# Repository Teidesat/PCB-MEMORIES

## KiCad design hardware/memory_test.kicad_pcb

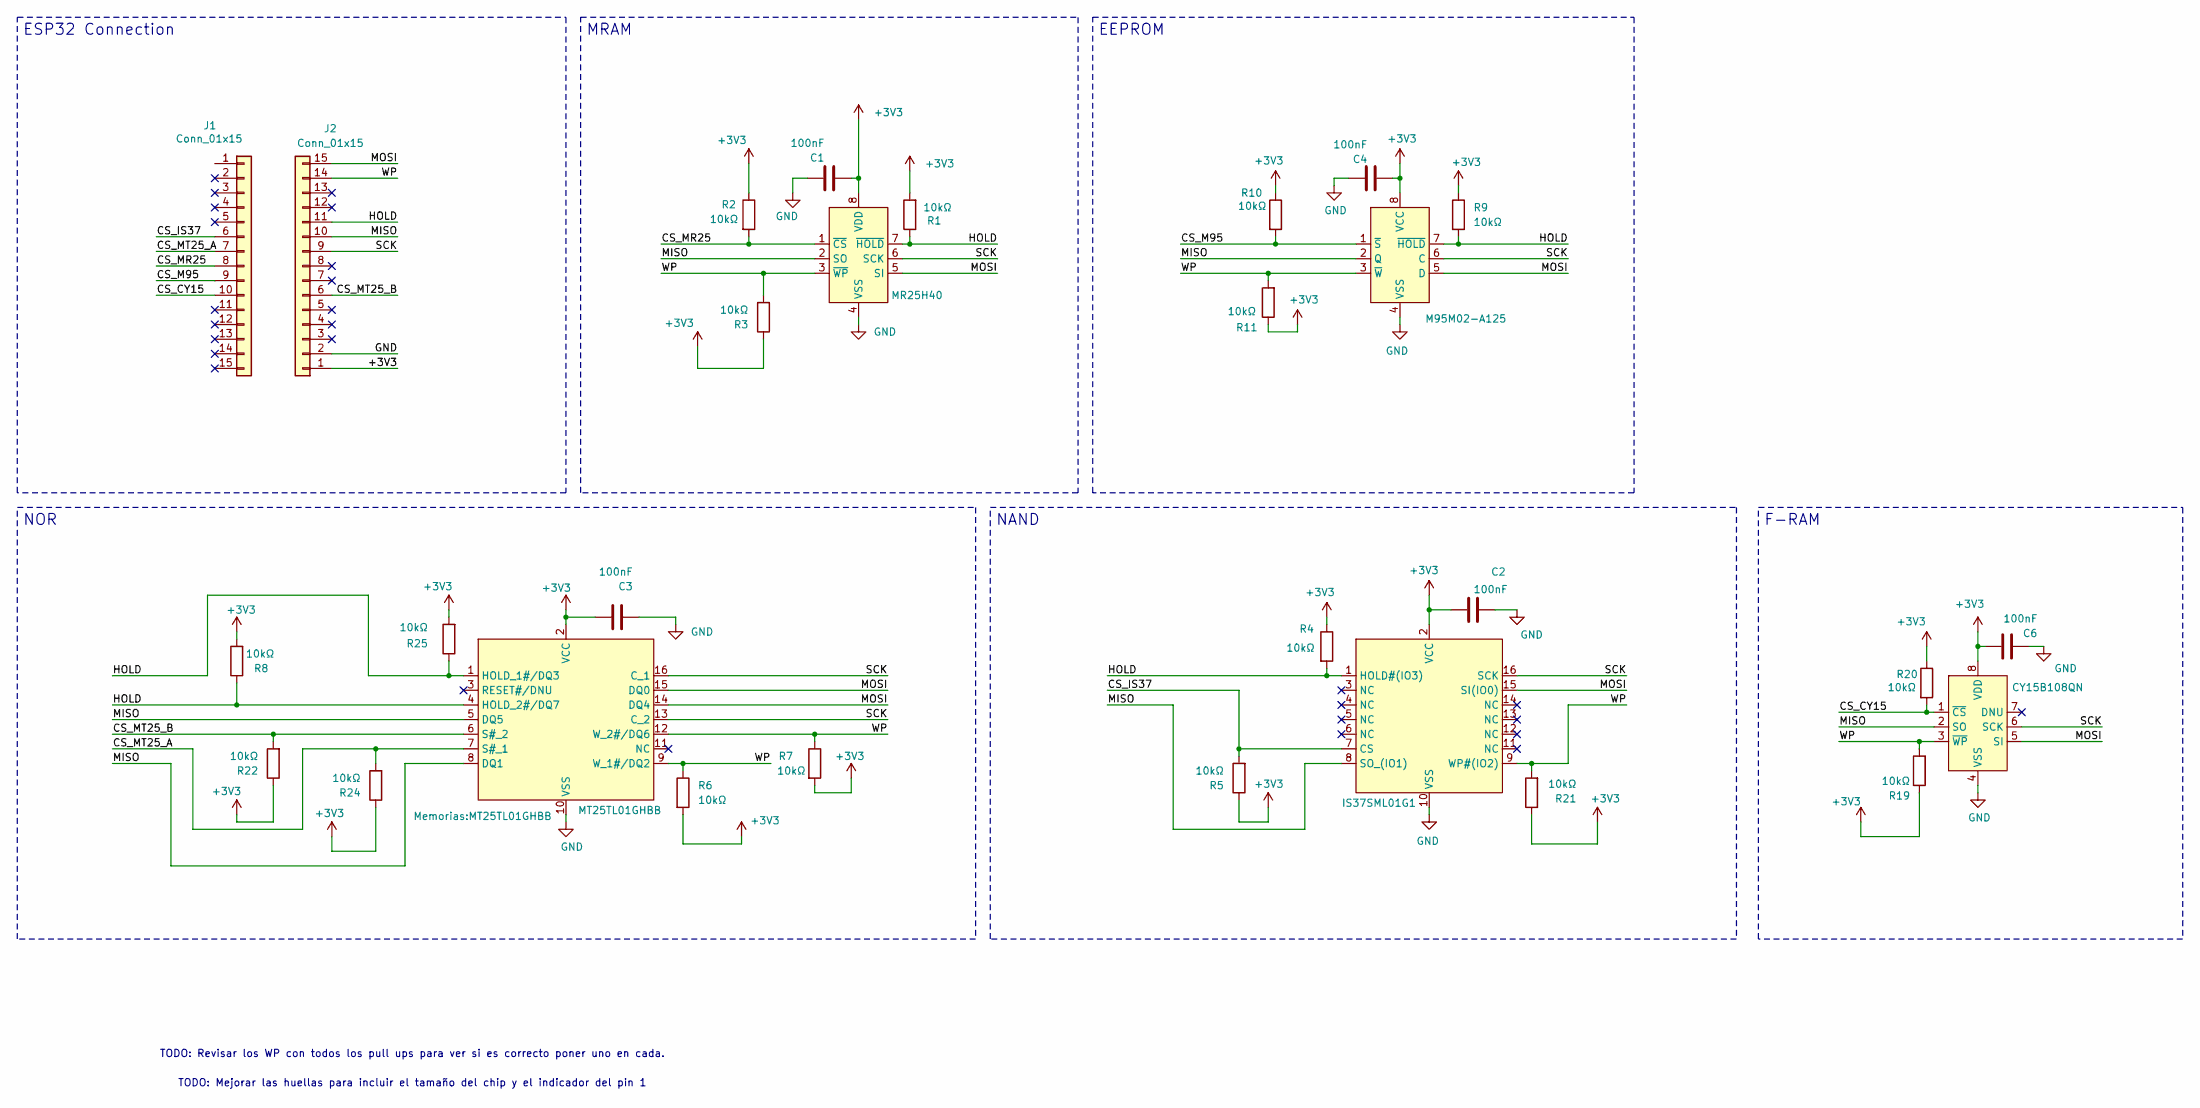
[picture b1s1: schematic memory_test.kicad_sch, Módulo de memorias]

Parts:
C1, C2, C3, C4, C6: 100nF; C_0805_2012Metric_Pad1.18x1.45mm_HandSolder
J1, J2: Conn_01x15; PinSocket_1x15_P2.54mm_Vertical
R1, R2, R3, R4, R5, R6, R7, R8, R9, R10, R11, R19, R20, R21, R22, R24, R25: 10kΩ; R_0805_2012Metric_Pad1.20x1.40mm_HandSolder
U1: MR25H40
U2: IS37SML01G1
U3: MT25TL01GHBB
U4: M95M02-A125
U6: CY15B108QN

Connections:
+3V3: C1.2, C2.2, C3.2, C4.2, C6.1, J2.1, R1.2, R2.1, R3.1, R4.1, R5.1, R6.2, R7.2, R8.2, R9.1, R10.1, R11.1, R19.1, R20.1, R21.1, R22.1, R24.1, R25.2, U1.8 (VDD), U2.2 (VCC), U3.2 (VCC), U4.8 (VCC), U6.8 (VDD)
/CS_CY15: J1.10, R20.2, U6.1 (~CS)
/CS_IS37: J1.6, R5.2, U2.7 (CS)
/CS_M95: J1.9, R10.2, U4.1 (~S)
/CS_MR25: J1.8, R2.2, U1.1 (~CS)
/CS_MT25_A: J1.7, R24.2, U3.7 (S#_1)
/CS_MT25_B: J2.6, R22.2, U3.6 (S#_2)
/HOLD: J2.11, R1.1, R4.2, R8.1, R9.2, R25.1, U1.7 (~HOLD), U2.1 (HOLD#(IO3)), U3.1 (HOLD_1#/DQ3), U3.4 (HOLD_2#/DQ7), U4.7 (~HOLD)
/MISO: J2.10, U1.2 (SO), U2.8 (SO_(IO1)), U3.5 (DQ5), U3.8 (DQ1), U4.2 (Q), U6.2 (SO)
/MOSI: J2.15, U1.5 (SI), U2.15 (SI(IO0)), U3.14 (DQ4), U3.15 (DQ0), U4.5 (D), U6.5 (SI)
/SCK: J2.9, U1.6 (SCK), U2.16 (SCK), U3.13 (C_2), U3.16 (C_1), U4.6 (C), U6.6 (SCK)
/WP: J2.14, R3.2, R6.1, R7.1, R11.2, R19.2, R21.2, U1.3 (~WP), U2.9 (WP#(IO2)), U3.9 (W_1#/DQ2), U3.12 (W_2#/DQ6), U4.3 (~W), U6.3 (~WP)
GND: C1.1, C2.1, C3.1, C4.1, C6.2, J2.2, U1.4 (VSS), U2.10 (VSS), U3.10 (VSS), U4.4 (VSS), U6.4 (VSS)

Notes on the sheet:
TODO: Revisar los WP con todos los pull ups para ver si es correcto poner uno en cada.
TODO: Mejorar las huellas para incluir el tamaño del chip y el indicador del pin 1
MRAM
EEPROM
F-RAM
NOR
ESP32 Connection
NAND

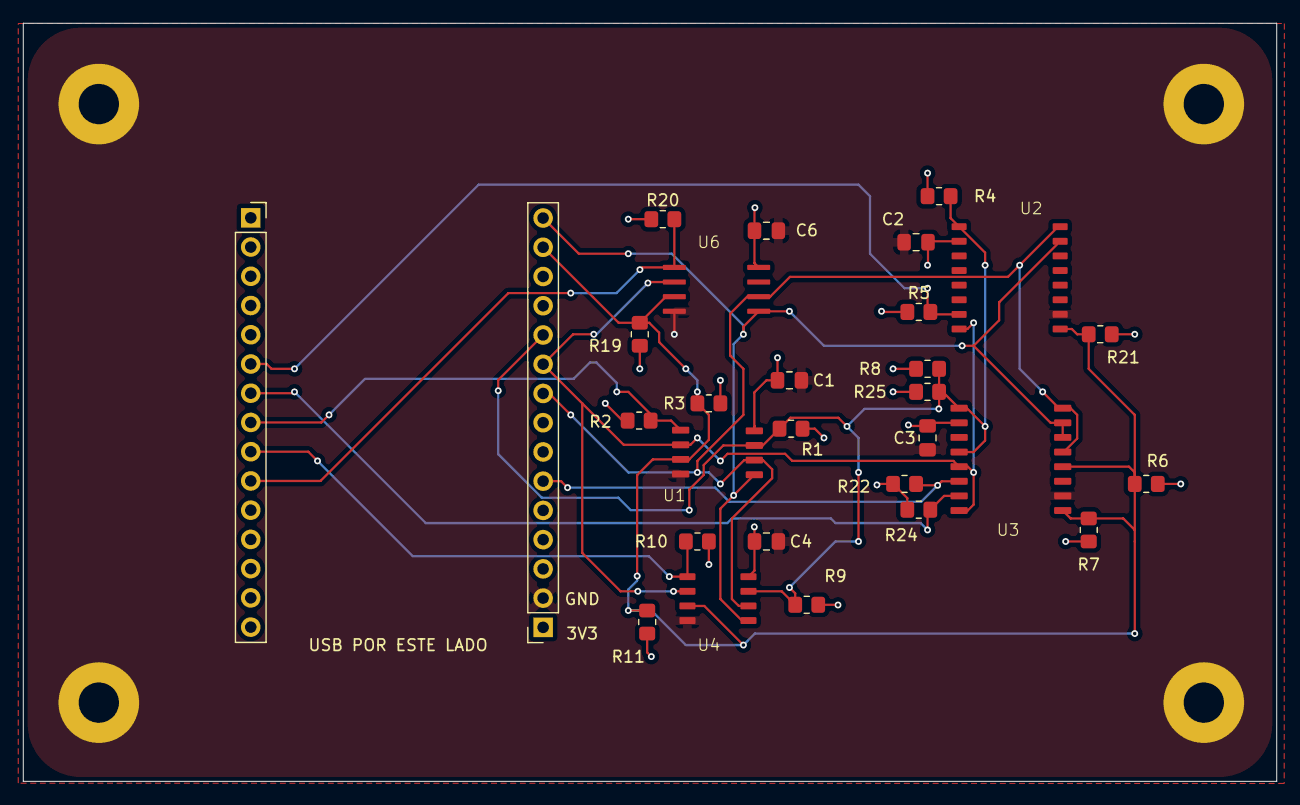
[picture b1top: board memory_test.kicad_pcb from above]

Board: 2 copper layers, 108.9 x 65.9 mm, 29 parts (0 on the bottom side), 13 nets.
